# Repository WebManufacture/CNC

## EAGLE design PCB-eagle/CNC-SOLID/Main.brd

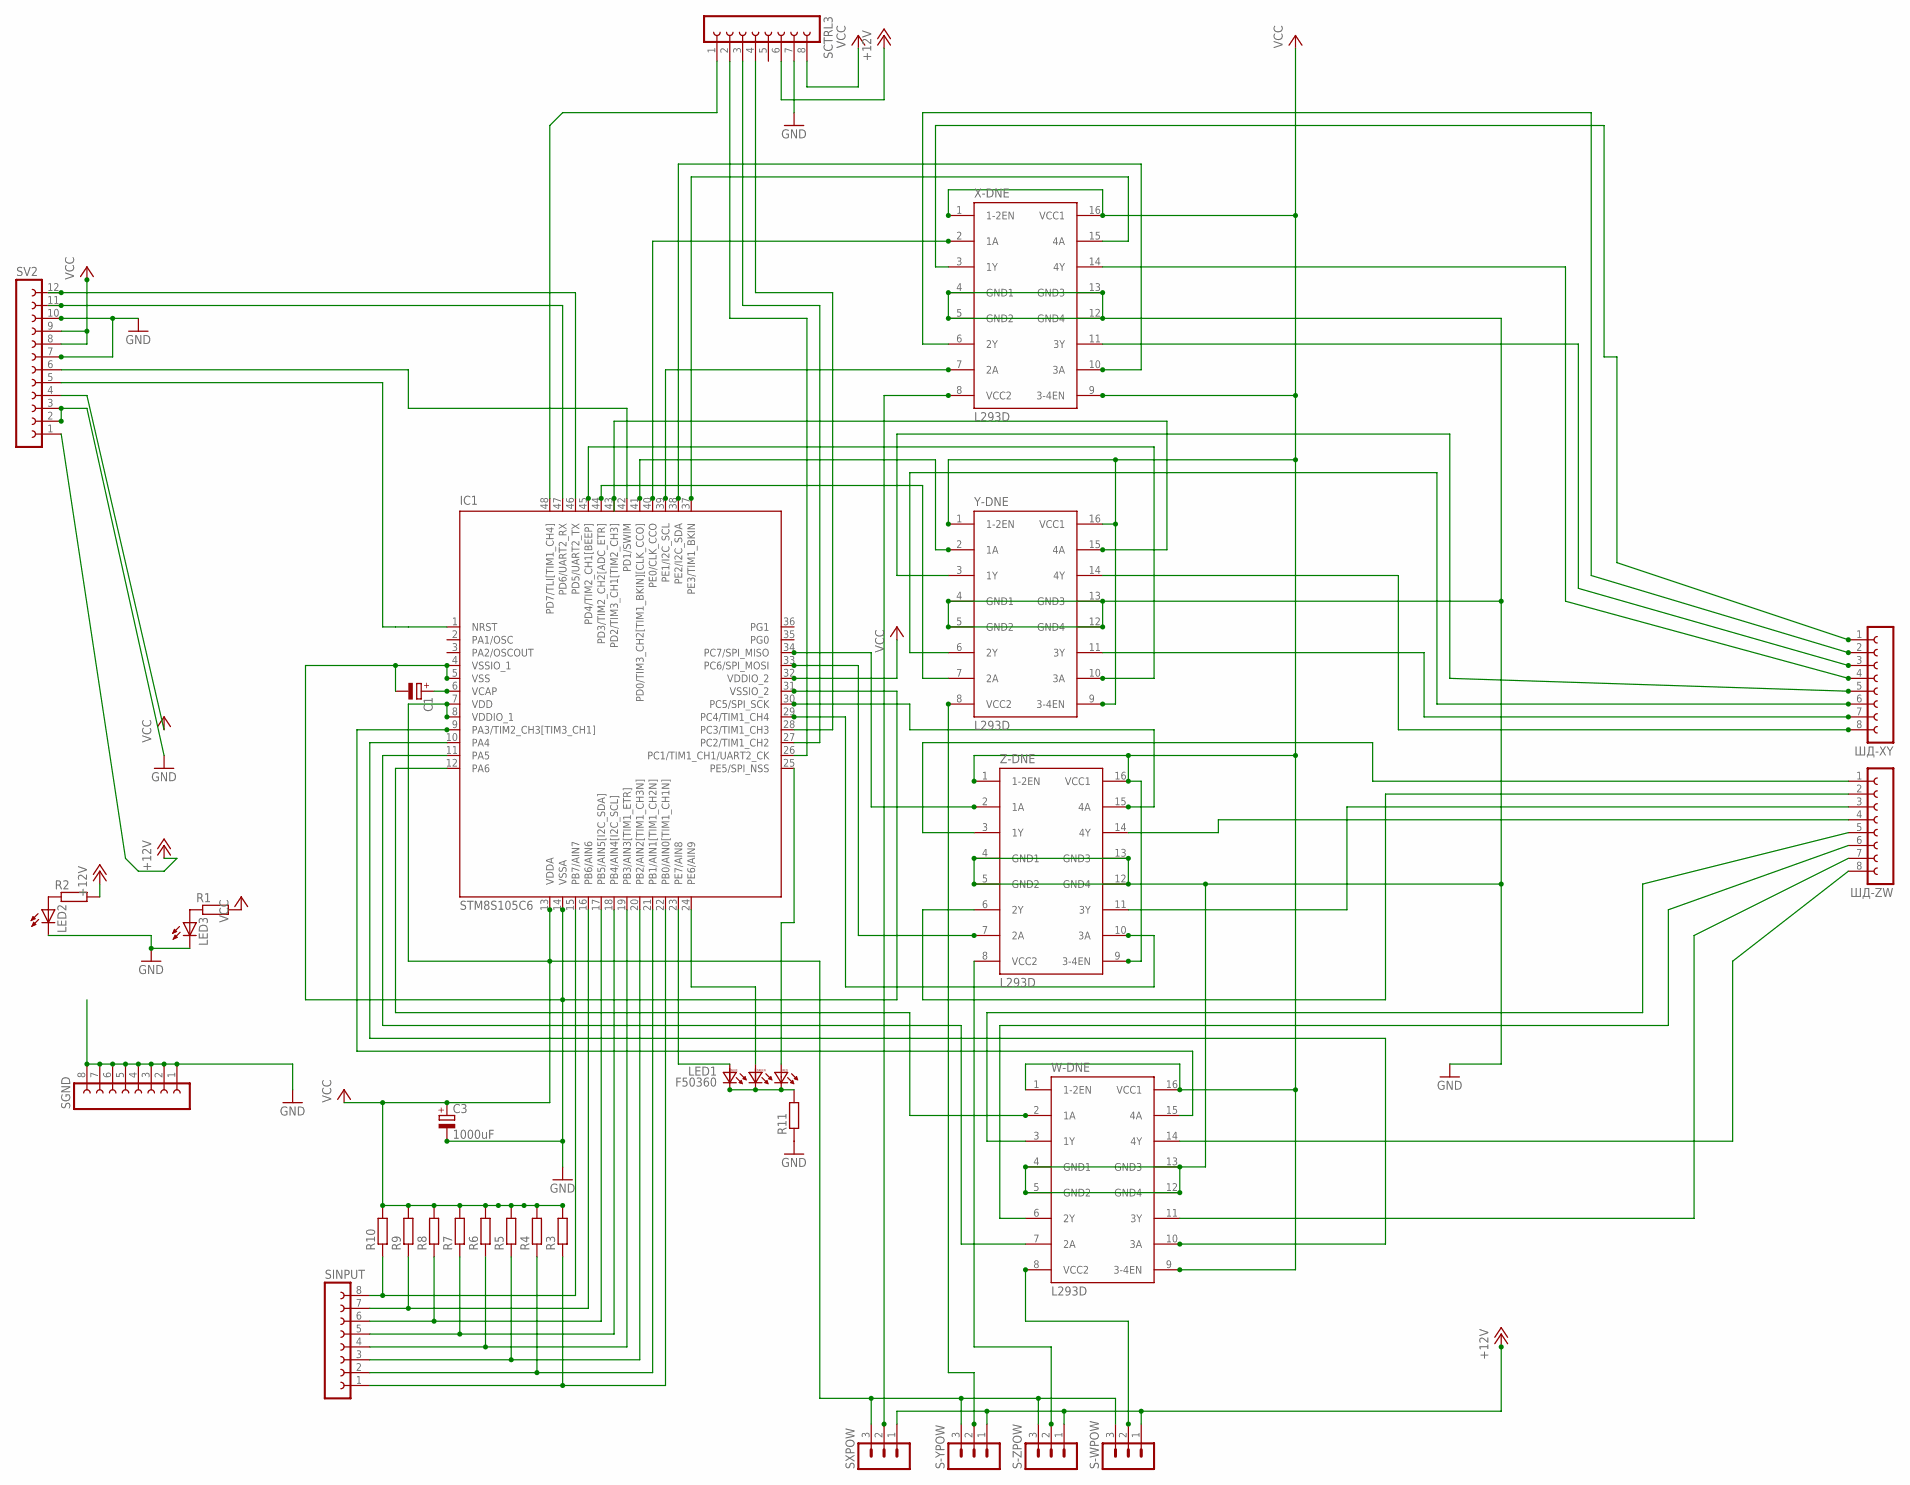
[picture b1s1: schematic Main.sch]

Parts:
C1: CPOL-EU085CS-1AR; 085CS_1AR
C3: 1000uF; SANYO-OSCON_9E
IC1: STM8S105C6; LQFP48-7X7
LED1: F50360
LED2, LED3: LED3MM
R1, R2, R11: R-EU_0204/7; 0204/7
R3, R4, R5, R6, R7, R8, R9, R10: R-EU_M0805; M0805
S-WPOW: MA03-1
S-YPOW: MA03-1
S-ZPOW: MA03-1
SCTRL3: FE08-1; FE08
SGND: FE08-1; FE08
SINPUT: FE08-1; FE08
SV2: FE12-1; FE12
SXPOW: MA03-1
W-DNE: L293D; DIL16
X-DNE: L293D; DIL16
Y-DNE: L293D; DIL16
Z-DNE: L293D; DIL16
ШД-XY: FE08-1; FE08
ШД-ZW: FE08-1; FE08

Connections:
+12V: R2.2, S-WPOW.1, S-YPOW.1, S-ZPOW.1, SCTRL3.6, SV2.1, SXPOW.1
GND: C1.-, C3.-, IC1.4 (VSSIO_1), IC1.5 (VSS), IC1.14 (VSSA), IC1.31 (VSSIO_2), LED2.K (C), LED3.K (C), R11.1, SCTRL3.7, SGND.1, SGND.2, SGND.3, SGND.4, SGND.5, SGND.6, SGND.7, SGND.8, SV2.2, SV2.3, SV2.7, SV2.10, W-DNE.4 (GND1), W-DNE.5 (GND2), W-DNE.12 (GND4), W-DNE.13 (GND3), X-DNE.4 (GND1), X-DNE.5 (GND2), X-DNE.12 (GND4), X-DNE.13 (GND3), Y-DNE.4 (GND1), Y-DNE.5 (GND2), Y-DNE.12 (GND4), Y-DNE.13 (GND3), Z-DNE.4 (GND1), Z-DNE.5 (GND2), Z-DNE.12 (GND4), Z-DNE.13 (GND3)
IN-Y1: IC1.41 (PD0/TIM3_CH2[TIM1_BKIN][CLK_CCO]), Y-DNE.2 (1A)
IN-Y2: IC1.44 (PD3/TIM2_CH2[ADC_ETR]), Y-DNE.7 (2A)
IN-Y3: IC1.45 (PD4/TIM2_CH1[BEEP]), Y-DNE.10 (3A)
IN-Y4: IC1.43 (PD2/TIM3_CH1[TIM2_CH3]), Y-DNE.15 (4A)
unnamed: IC1.22 (PB0/AIN0[TIM1_CH1N]), R3.1, SINPUT.1
unnamed: IC1.47 (PD6/UART2_RX), SV2.11
unnamed: C1.+, IC1.6 (VCAP)
unnamed: IC1.40 (PE0/CLK_CCO), X-DNE.2 (1A)
unnamed: IC1.39 (PE1/I2C_SCL), X-DNE.7 (2A)
unnamed: IC1.38 (PE2/I2C_SDA), X-DNE.10 (3A)
unnamed: IC1.37 (PE3/TIM1_BKIN), X-DNE.15 (4A)
unnamed: IC1.34 (PC7/SPI_MISO), Z-DNE.2 (1A)
unnamed: IC1.33 (PC6/SPI_MOSI), Z-DNE.7 (2A)
unnamed: IC1.30 (PC5/SPI_SCK), Z-DNE.15 (4A)
unnamed: IC1.29 (PC4/TIM1_CH4), Z-DNE.10 (3A)
unnamed: IC1.9 (PA3/TIM2_CH3[TIM3_CH1]), W-DNE.15 (4A)
unnamed: IC1.10 (PA4), W-DNE.10 (3A)
unnamed: IC1.11 (PA5), W-DNE.7 (2A)
unnamed: IC1.12 (PA6), W-DNE.2 (1A)
unnamed: IC1.21 (PB1/AIN1[TIM1_CH2N]), R4.1, SINPUT.2
unnamed: IC1.20 (PB2/AIN2[TIM1_CH3N]), R5.1, SINPUT.3
unnamed: IC1.19 (PB3/AIN3[TIM1_ETR]), R6.1, SINPUT.4
unnamed: IC1.18 (PB4/AIN4[I2C_SCL]), R7.1, SINPUT.5
unnamed: IC1.17 (PB5/AIN5[I2C_SDA]), R8.1, SINPUT.6
unnamed: IC1.16 (PB6/AIN6), R9.1, SINPUT.7
unnamed: IC1.15 (PB7/AIN7), R10.1, SINPUT.8
unnamed: LED1.BC, LED1.GC, LED1.RC, R11.2
unnamed: IC1.23 (PE7/AIN8), LED1.BA
unnamed: IC1.24 (PE6/AIN9), LED1.GA
unnamed: IC1.25 (PE5/SPI_NSS), LED1.RA
unnamed: IC1.48 (PD7/TLI[TIM1_CH4]), SCTRL3.1
unnamed: IC1.27 (PC2/TIM1_CH2), SCTRL3.3
unnamed: IC1.28 (PC3/TIM1_CH3), SCTRL3.4
unnamed: LED3.A, R1.1
unnamed: LED2.A, R2.1
unnamed: IC1.26 (PC1/TIM1_CH1/UART2_CK), SCTRL3.2
PW1: W-DNE.3 (1Y), ШД-ZW.5
PW2: W-DNE.6 (2Y), ШД-ZW.6
PW3: W-DNE.11 (3Y), ШД-ZW.7
PW4: W-DNE.14 (4Y), ШД-ZW.8
PX1: X-DNE.3 (1Y), ШД-XY.1
PX2: X-DNE.6 (2Y), ШД-XY.2
PX3: X-DNE.11 (3Y), ШД-XY.3
PX4: X-DNE.14 (4Y), ШД-XY.4
PY1: Y-DNE.3 (1Y), ШД-XY.5
PY2: Y-DNE.6 (2Y), ШД-XY.6
PY3: Y-DNE.11 (3Y), ШД-XY.7
PY4: Y-DNE.14 (4Y), ШД-XY.8
PZ1: Z-DNE.3 (1Y), ШД-ZW.1
PZ2: Z-DNE.6 (2Y), ШД-ZW.2
PZ3: Z-DNE.11 (3Y), ШД-ZW.3
PZ4: Z-DNE.14 (4Y), ШД-ZW.4
RST: IC1.1 (NRST), SV2.5
SWD: IC1.42 (PD1/SWIM), SV2.6
TXD: IC1.46 (PD5/UART2_TX), SV2.12
VCC: C3.+, IC1.7 (VDD), IC1.8 (VDDIO_1), IC1.13 (VDDA), IC1.32 (VDDIO_2), R1.2, R3.2, R4.2, R5.2, R6.2, R7.2, R8.2, R9.2, R10.2, S-WPOW.3, S-YPOW.3, S-ZPOW.3, SCTRL3.8, SV2.4, SV2.8, SV2.9, SXPOW.3, W-DNE.1 (1-2EN), W-DNE.9 (3-4EN), W-DNE.16 (VCC1), X-DNE.1 (1-2EN), X-DNE.9 (3-4EN), X-DNE.16 (VCC1), Y-DNE.1 (1-2EN), Y-DNE.9 (3-4EN), Y-DNE.16 (VCC1), Z-DNE.1 (1-2EN), Z-DNE.9 (3-4EN), Z-DNE.16 (VCC1)
VCC_W_SEL: S-WPOW.2, W-DNE.8 (VCC2)
VCC_X_SEL: SXPOW.2, X-DNE.8 (VCC2)
VCC_Y_SEL: S-YPOW.2, Y-DNE.8 (VCC2)
VCC_Z_SEL: S-ZPOW.2, Z-DNE.8 (VCC2)

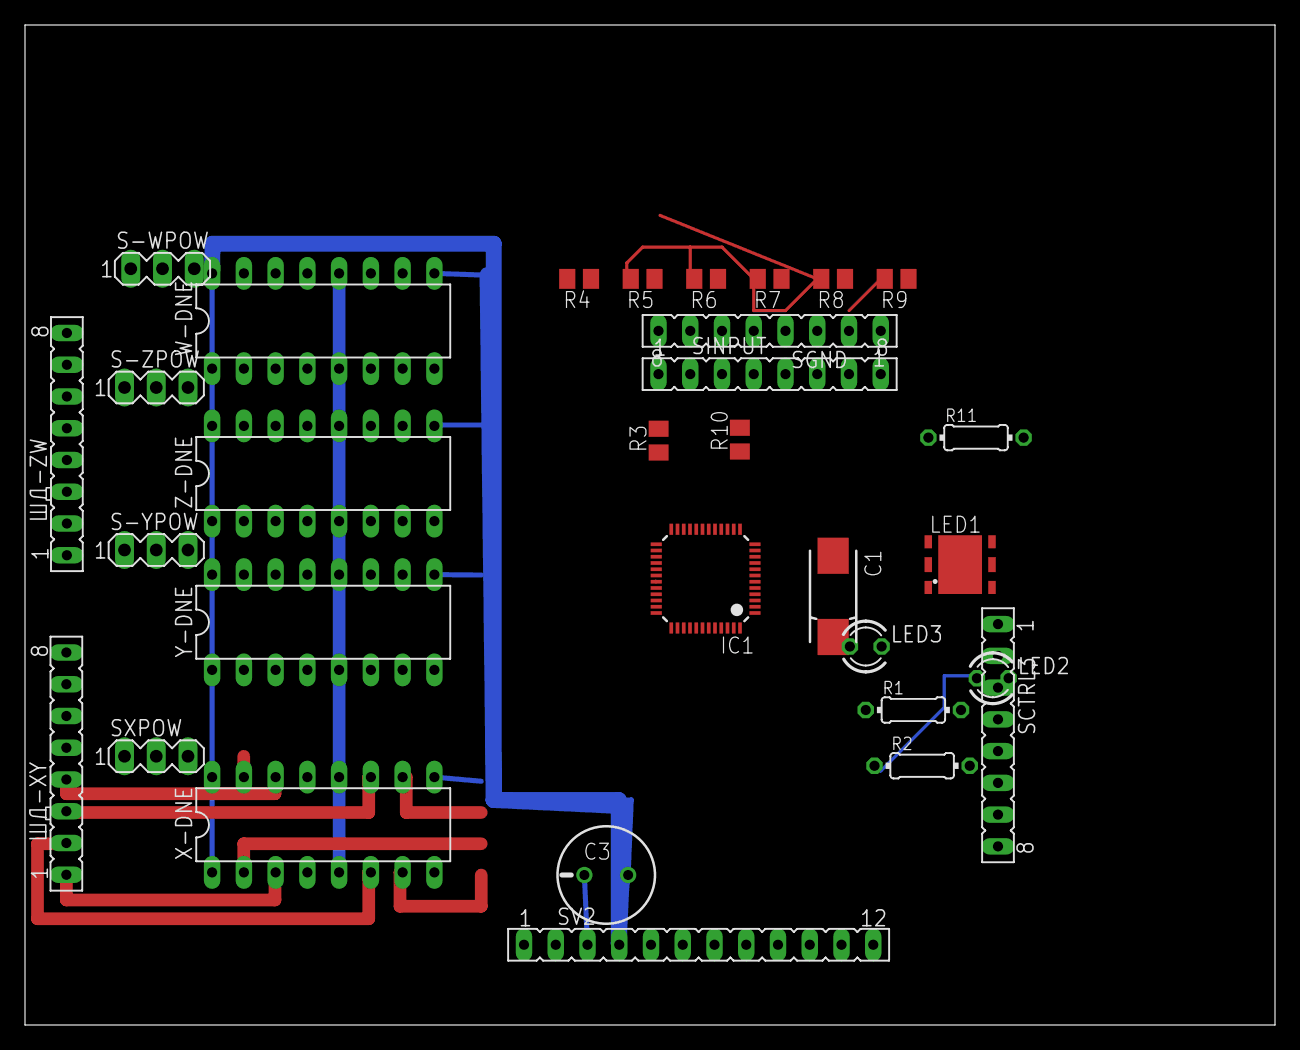
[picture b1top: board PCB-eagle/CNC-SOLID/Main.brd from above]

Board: 2 copper layers, 100.0 x 80.0 mm, 31 parts (0 on the bottom side), 62 nets.

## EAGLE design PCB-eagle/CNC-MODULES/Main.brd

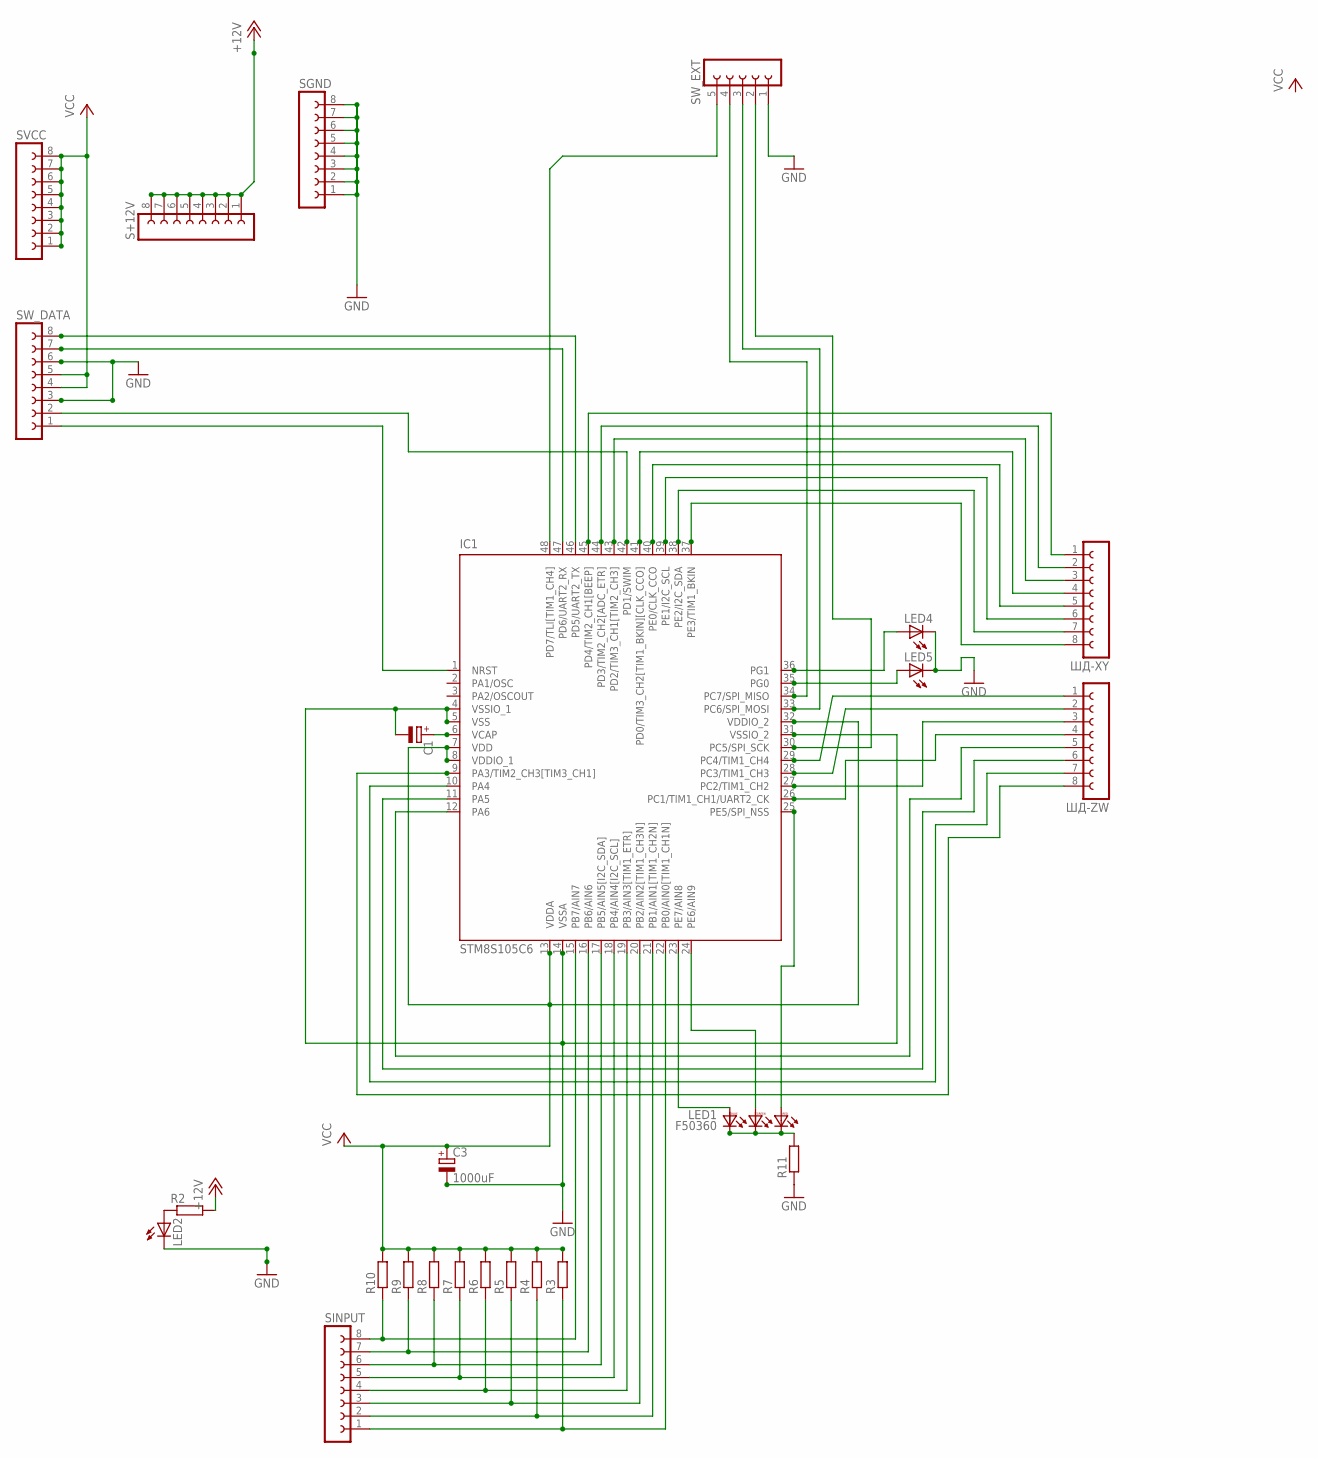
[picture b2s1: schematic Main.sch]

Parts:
C1: CPOL-EUR/2012-12W; R/2012-12W
C3: 1000uF; SANYO-OSCON_9E
IC1: STM8S105C6; LQFP48-7X7
LED1: F50360
LED2, LED4, LED5: LED3MM
R2, R11: R-EU_0204/7; 0204/7
R3, R4, R5, R6, R7, R8, R9, R10: R-EU_M0805; M0805
S+12V: FE08-1; FE08
SGND: FE08-1; FE08
SINPUT: FE08-1; FE08
SVCC: FE08-1; FE08
SW_DATA: FE08-1; FE08
SW_EXT: FE05-1
ШД-XY: FE08-1; FE08
ШД-ZW: FE08-1; FE08

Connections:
+12V: R2.2, S+12V.1, S+12V.2, S+12V.3, S+12V.4, S+12V.5, S+12V.6, S+12V.7, S+12V.8
GND: C1.-, C3.-, IC1.4 (VSSIO_1), IC1.5 (VSS), IC1.14 (VSSA), IC1.31 (VSSIO_2), LED2.K (C), LED4.K (C), LED5.K (C), R11.1, SGND.1, SGND.2, SGND.3, SGND.4, SGND.5, SGND.6, SGND.7, SGND.8, SW_DATA.3, SW_DATA.6, SW_EXT.1
IN-Y3: IC1.45 (PD4/TIM2_CH1[BEEP]), ШД-XY.1
IN-Y4: IC1.43 (PD2/TIM3_CH1[TIM2_CH3]), ШД-XY.3
LED_GND: LED1.BC, LED1.GC, LED1.RC, R11.2
unnamed: IC1.22 (PB0/AIN0[TIM1_CH1N]), R3.1, SINPUT.1
unnamed: IC1.47 (PD6/UART2_RX), SW_DATA.7
unnamed: C1.+, IC1.6 (VCAP)
unnamed: IC1.40 (PE0/CLK_CCO), ШД-XY.5
unnamed: IC1.39 (PE1/I2C_SCL), ШД-XY.6
unnamed: IC1.38 (PE2/I2C_SDA), ШД-XY.7
unnamed: IC1.37 (PE3/TIM1_BKIN), ШД-XY.8
unnamed: IC1.34 (PC7/SPI_MISO), SW_EXT.4
unnamed: IC1.35 (PG0), LED5.A
unnamed: IC1.26 (PC1/TIM1_CH1/UART2_CK), ШД-ZW.4
unnamed: IC1.9 (PA3/TIM2_CH3[TIM3_CH1]), ШД-ZW.8
unnamed: IC1.27 (PC2/TIM1_CH2), ШД-ZW.3
unnamed: IC1.11 (PA5), ШД-ZW.6
unnamed: IC1.12 (PA6), ШД-ZW.5
unnamed: IC1.28 (PC3/TIM1_CH3), ШД-ZW.2
unnamed: IC1.41 (PD0/TIM3_CH2[TIM1_BKIN][CLK_CCO]), ШД-XY.4
unnamed: IC1.29 (PC4/TIM1_CH4), ШД-ZW.1
unnamed: IC1.30 (PC5/SPI_SCK), SW_EXT.2
unnamed: IC1.36 (PG1), LED4.A
unnamed: IC1.21 (PB1/AIN1[TIM1_CH2N]), R4.1, SINPUT.2
unnamed: IC1.20 (PB2/AIN2[TIM1_CH3N]), R5.1, SINPUT.3
unnamed: IC1.19 (PB3/AIN3[TIM1_ETR]), R6.1, SINPUT.4
unnamed: IC1.18 (PB4/AIN4[I2C_SCL]), R7.1, SINPUT.5
unnamed: IC1.17 (PB5/AIN5[I2C_SDA]), R8.1, SINPUT.6
unnamed: IC1.16 (PB6/AIN6), R9.1, SINPUT.7
unnamed: IC1.15 (PB7/AIN7), R10.1, SINPUT.8
unnamed: IC1.23 (PE7/AIN8), LED1.BA
unnamed: IC1.24 (PE6/AIN9), LED1.GA
unnamed: IC1.25 (PE5/SPI_NSS), LED1.RA
unnamed: IC1.48 (PD7/TLI[TIM1_CH4]), SW_EXT.5
unnamed: IC1.33 (PC6/SPI_MOSI), SW_EXT.3
unnamed: IC1.10 (PA4), ШД-ZW.7
unnamed: IC1.44 (PD3/TIM2_CH2[ADC_ETR]), ШД-XY.2
unnamed: LED2.A, R2.1
RST: IC1.1 (NRST), SW_DATA.1
SWD: IC1.42 (PD1/SWIM), SW_DATA.2
TXD: IC1.46 (PD5/UART2_TX), SW_DATA.8
VCC: C3.+, IC1.7 (VDD), IC1.8 (VDDIO_1), IC1.13 (VDDA), IC1.32 (VDDIO_2), R3.2, R4.2, R5.2, R6.2, R7.2, R8.2, R9.2, R10.2, SVCC.1, SVCC.2, SVCC.3, SVCC.4, SVCC.5, SVCC.6, SVCC.7, SVCC.8, SW_DATA.4, SW_DATA.5

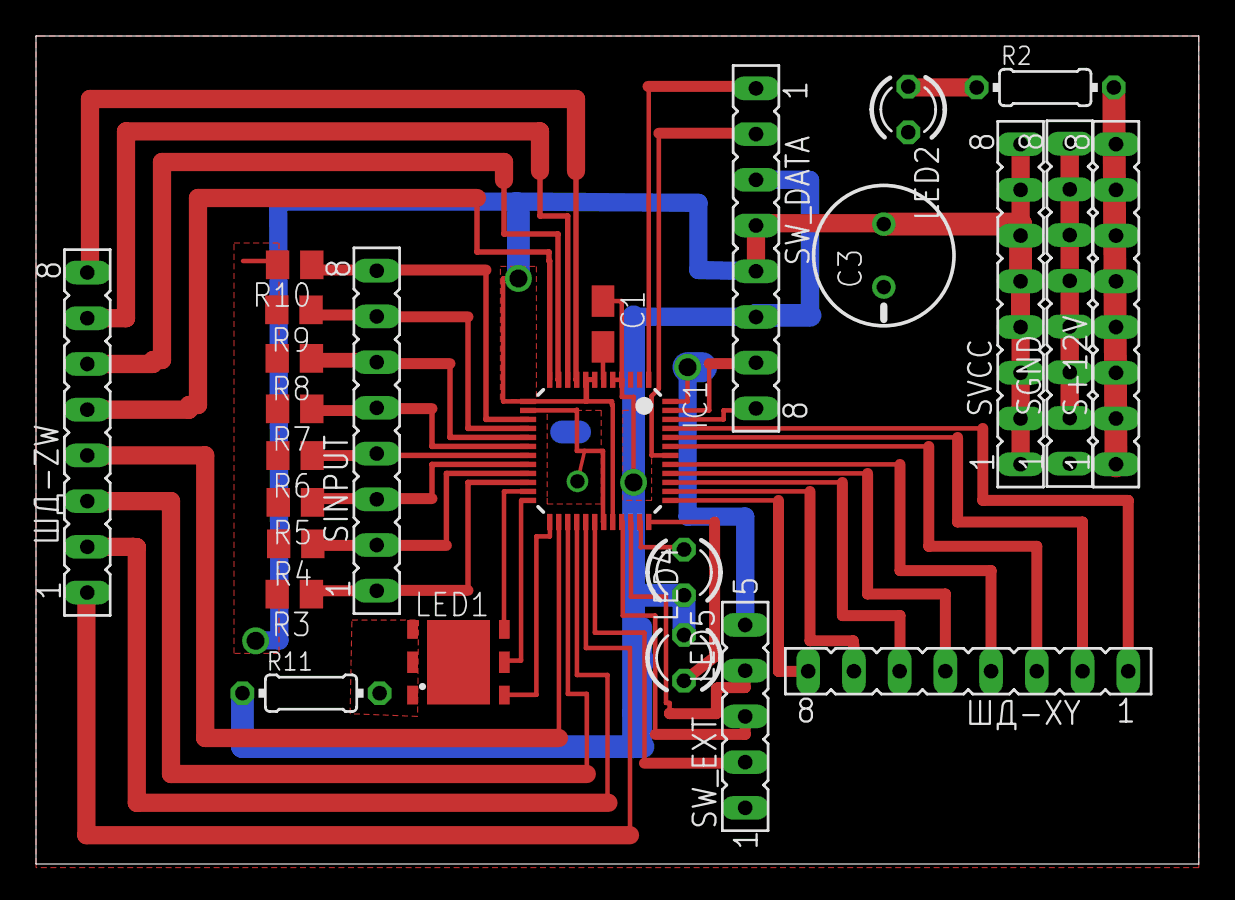
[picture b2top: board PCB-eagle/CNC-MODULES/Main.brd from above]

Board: 2 copper layers, 64.6 x 46.0 mm, 25 parts (0 on the bottom side), 43 nets.

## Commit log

2014-04-17 Last Version with callbacks
2014-11-03 Working copy with time parameter.
2014-11-04 Worked ver vith async motor. Prepare to ASM
2017-08-29 Added all settings and models library
2017-08-30 Svn ignore
2019-09-30 CNC Controller integrated
2019-09-30 Actualization
